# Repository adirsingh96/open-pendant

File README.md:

# OpenPendant

https://github.com/user-attachments/assets/51f84d97-9171-487b-b558-6a6707e0dcb2

The launch film: it listens only when you ask, the meeting stays on your phone, you bring your own keys, and the board, case, and firmware are open source.

Open-source DIY AI audio pendant. Firmware runs on a **Seeed XIAO nRF52840 Sense**. The necklace captures audio and streams 16 kHz PCM over BLE. Speech-to-text runs on the **phone or laptop**. The MCU never holds an API key.

Record only with an obvious LED and an explicit host subscribe (GATT notify on = recording).

## Hardware

| Part | Notes |
|------|--------|
| Seeed XIAO nRF52840 Sense | nRF52840 + onboard PDM mic + LSM6DS3TR-C IMU |
| microSD SPI/SDIO module | 8-pin breakout; VCC = **3V3 only** (never 5V) |
| Ø6 tactile button | 2-pin NO; COM → GND, NO → D1 |
| 22 µF capacitor | Across SD **3V3** and **GND** (16 V ceramic preferred) |
| Perfboard strip | ~8 × 18 holes; XIAO + SD on the front, LiPo on the back |
| WLY602030 1S LiPo | 3.7 V nominal, 300 mAh, 6 × 20 × 30 mm. Open-wire to **BAT+/BAT−**. USB-C charges via BQ25101. |
| USB-C cable | Dev and UF2 flash |

The table above is the first bench build on perfboard. The wearable replaces that strip and the SD breakout with the carrier below. Do not order the older 30 × 45 mm board.

| Build file | What it is |
|------------|------------|
| [`openpendant_carrier-gerbers.zip`](hardware/openpendant_carrier/openpendant_carrier/output/openpendant_carrier-gerbers.zip) | JLCPCB gerbers. Bare boards, 2-layer, 1.6 mm, 1 oz, lead-free HASL. Assembly off. |
| [`openpendant_carrier.kicad_pro`](hardware/openpendant_carrier/openpendant_carrier/openpendant_carrier.kicad_pro) | KiCad source |
| [`docs/carrier_assembly.html`](docs/carrier_assembly.html) | What arrives, what you solder, and the pin map |
| [`cad/character/`](hardware/openpendant_carrier/cad/character/) | Case to print: `character_front.3mf`, `character_back.stl`, `character_button_hat.stl`. Read `PRINT.txt` in that folder. |

Print the character case (Orbit O). PETG, 0.4 mm nozzle, 0.2 mm layers, no supports. Front skirt on the bed. Back chest-down so the chain bail sits on the bed. That folder is the only case in the repo.

Assembly guide for the first perfboard build: [`docs/pendant_assembly.html`](docs/pendant_assembly.html).

### Wiring (USB at the bottom)

Pin map with the component face toward you:

```text
  XIAO                              microSD (SPI)
  ----                              -------------
  D9  (SCK)  ---------------------> CLK
  D8  (MOSI) ---------------------> CMD
  D7  (MISO) ---------------------> D0
  D6  (CS)   ---------------------> D3
  3V3 ----------------------------> 3V3
  GND ----------------------------> GND
                                    D1, D2  (leave open)

  Button NO  ---------------------> D1
  Button COM ---------------------> GND

  22 µF  across SD 3V3 ↔ SD GND

  LiPo red  --> BAT+     (through the BAT window, last)
  LiPo black -> BAT−
```

```text
Left (USB bottom)       Right (USB bottom)
─────────────────       ──────────────────
D6 ──► SD D3 (CS)       D7 ──► SD D0
D5  (IMU SCL — open)    D8 ──► SD CMD
D4  (IMU SDA — open)    D9 ──► SD CLK
D3                      D10
D2                      3V3 ──► SD 3V3
D1  button NO           GND
D0                      5V   (empty)
```

Firmware remaps SPI2 onto **D9 / D8 / D7** (not the board silk SPI defaults D8 / D10 / D9) and disables UART0 so it cannot steal **D6 / D7**. After soldering, flash over USB (no cell required) and run **Settings → Developer → Run SD test** with a FAT32 card.

## What you get

- **Firmware** (Zephyr / nRF Connect SDK 3.4, Zephyr 4.4): BLE GATT PCM + status, IMU still-sleep (mic off when the board is still, wake on motion), battery voltage / SoC estimate, microSD FAT R/W self-test, **offline meeting/note PCM on SD** with BLE sync (`70301105`).
- **Flutter app** in [`app/`](app/): meetings and hold-to-talk notes over BLE, local VAD, **Saaras v4** or on-device **Qwen3-ASR**, reminders, daily briefings and recaps, persistent follow-ups, Memories search, local SQLite, and **pull of offline SD clips on reconnect**. Meetings stay one transcript. Speaker diarization is not applied.
- **Laptop tools** in [`tools/`](tools/): BLE capture to WAV, OpenAI or local Whisper.

Protocol, clip schema, and roadmap: [project_context.md](project_context.md). Later sync sketch: [docs/sync_api.md](docs/sync_api.md).

## Firmware

Requires [nRF Connect SDK v3.4.0](https://docs.nordicsemi.com/bundle/ncs-latest/page/nrf/installation.html). Use the Nordic SoftDevice Controller only — do **not** enable `CONFIG_BT_LL_SW_SPLIT` on this board (USB CDC breaks).

```bash
west build -b xiao_ble/nrf52840/sense -d build .
```

Double-tap RESET so the volume `XIAO-SENSE` appears. Finder copy often fails; `dd` works:

```bash
dd if=$(find build -name zephyr.uf2 | head -1) of=/Volumes/XIAO-SENSE/CURRENT.UF2 bs=4096
```

Serial (macOS `screen` often hangs up CDC):

```bash
python3 -m serial.tools.miniterm /dev/cu.usbmodem1101 115200
```

BLE advertises as **OpenPendant**. Disconnect nRF Connect before the app or laptop capture (one connection).

**Control** UUID `70301104-…`:
- `0` / `1` — find-pendant LED flash off / on
- `2` — SD mount / write / read self-test (result in status bytes 8–9)
- `0x10` — list next pending offline clip (response on SD data notify)
- `0x11` + `id[8]` — open clip for read
- `0x12` + `offset_le32` + `len_le16` — read chunk
- `0x13` + `id[8]` — delete after phone has stored the clip

**SD data** UUID `70301105-…` (NOTIFY/READ): list/read framing for offline sync. Live PCM stays on `70301102`.

**Offline button UX** (when PCM notify is off): single click toggles a meeting session under `/SD:/op/m_…/`; long-press records a note `n_….pcm`. When the phone arms live PCM, offline capture stops (no dual-write).

### Offline → sync test (USB power, no LiPo)

1. FAT32 card in the SPI slot; flash firmware; leave BLE disconnected (or never connect).
2. Offline: click → talk → click (meeting); long-press a note. Red LED while meeting armed; blue while note held.
3. Connect the app → automatic sync (or **Developer → Sync SD**). Meetings/notes appear and transcribe like live captures.
4. Second sync imports nothing (deleted on card / `pendant_clip_id` dedup).
5. Regression: with BLE connected and Record armed, audio streams over PCM notify with **no** new SD writes.
## Flutter app

A meeting stays one transcript. Overview is the short recap, action items, and private notes. Ask about this meeting sits under either tab.

| Transcript | Overview |
|------------|----------|
|  |  |

```bash
cd app
flutter pub get
flutter run -d macos          # BLE works on Mac
# or a physical iPhone / Android — not the iOS simulator
```

Paste a **Sarvam** key in **Settings** (required for cloud transcripts) and an **OpenAI** key for day Clean, Memories, and meeting Recap. Keys stay on the host (Keychain / Keystore / app-support file on desktop), never on the pendant.

**Typical day**

1. Connect. Optional **Calibrate** (wear as usual, read the script) sets a personal VAD floor for **notes** only.
2. Optional **Voices**: enroll up to 4 people (2–10 s sample each). Meetings do not split one clip into speaker turns.
3. Start a **meeting** (pendant click, or **Start meeting** in the app) or take a **note** (hold the pendant ~0.7 s, or **Take a note** on the phone). Say “remind me to … at 10 AM” and the phone notifies 15 minutes before; notes without a time come back in an 8 AM reminder until you check them off. **Double-click** rings the connected phone so you can find it. **Find pendant** (connected sheet or Settings → More) is closer/farther from BLE signal, not a compass. Notify stays on while a meeting is armed; LED stays solid. Chunks rotate on IMU sleep, about 12 s of audio, or quiet after speech. Local VAD skips the cloud when there is no speech. Meetings use a fixed energy floor (`1e9`, ~0.5 s of speech) so people a metre or two from the chest mic still pass; hiss still has to look like voice. Wearer calibrate does not raise that meeting gate. Double-click a meeting title to rename it.
4. **Transcription:** Settings can use **Saaras v4** (cloud) or **on-device Qwen3-ASR**. Both store the engine text as returned (Hindi in Devanagari when that is what came back). Stop the meeting when you are done. Home groups chunks into one transcript. The transcript tab shows **Transcribing…** until STT catches up.
5. **Close the day:** Home surfaces pending notes and open loops. Tap **Close today** to clean the day’s stored text and create chapters, decisions, follow-ups, and a Memories-ready recap. Follow-ups become checkable notes and join the 8 AM digest until completed. Open the saved review and use **Refresh recap** to replace it after recording more; each run uses OpenAI.

More setup (permissions, IMU debug): [app/README.md](app/README.md).

## Laptop capture

```bash
python3 -m pip install -r tools/requirements.txt
export OPENAI_API_KEY=          # optional; omit for local Whisper
python3 tools/capture_pcm.py --seconds 8 --out capture.wav && \
  python3 tools/transcribe.py capture.wav --backend openai
```

Local Whisper:

```bash
python3 tools/transcribe.py capture.wav --backend local
```

## Consent and sleep

- **Recording:** enable PCM notify. The red LED stays solid while subscribed (armed).
- **IMU sleep:** after ~10 s still, firmware stops the PDM mic and PCM. BLE stays up. Motion wakes the mic. Host VAD drops non-speech before STT.
- **App Sleep** is a BLE disconnect, not IMU sleep.

## Battery

Solder the WLY602030 **red** lead to **BAT+** and **black** to **BAT−** (polarity matters; open wire, no JST). USB-C charges the cell through the XIAO BQ25101. Connect the cell **last**, after the SD / button joints meter clean on USB.

The cell has no fuel-gauge IC. Firmware measures pack voltage (P0.31, 1 MΩ / 510 kΩ divider) and the app maps that to a **rough SoC only when USB is unplugged**. On USB the BQ25101 rail reads ~4.1 V even with no cell, so the UI shows **USB** instead of a fake percent. Treat ~20% as “charge soon.” Keep P0.14 low whenever a cell is attached (firmware hog does this) so P0.31 stays within 3.6 V.

## License

[Apache License 2.0](LICENSE).

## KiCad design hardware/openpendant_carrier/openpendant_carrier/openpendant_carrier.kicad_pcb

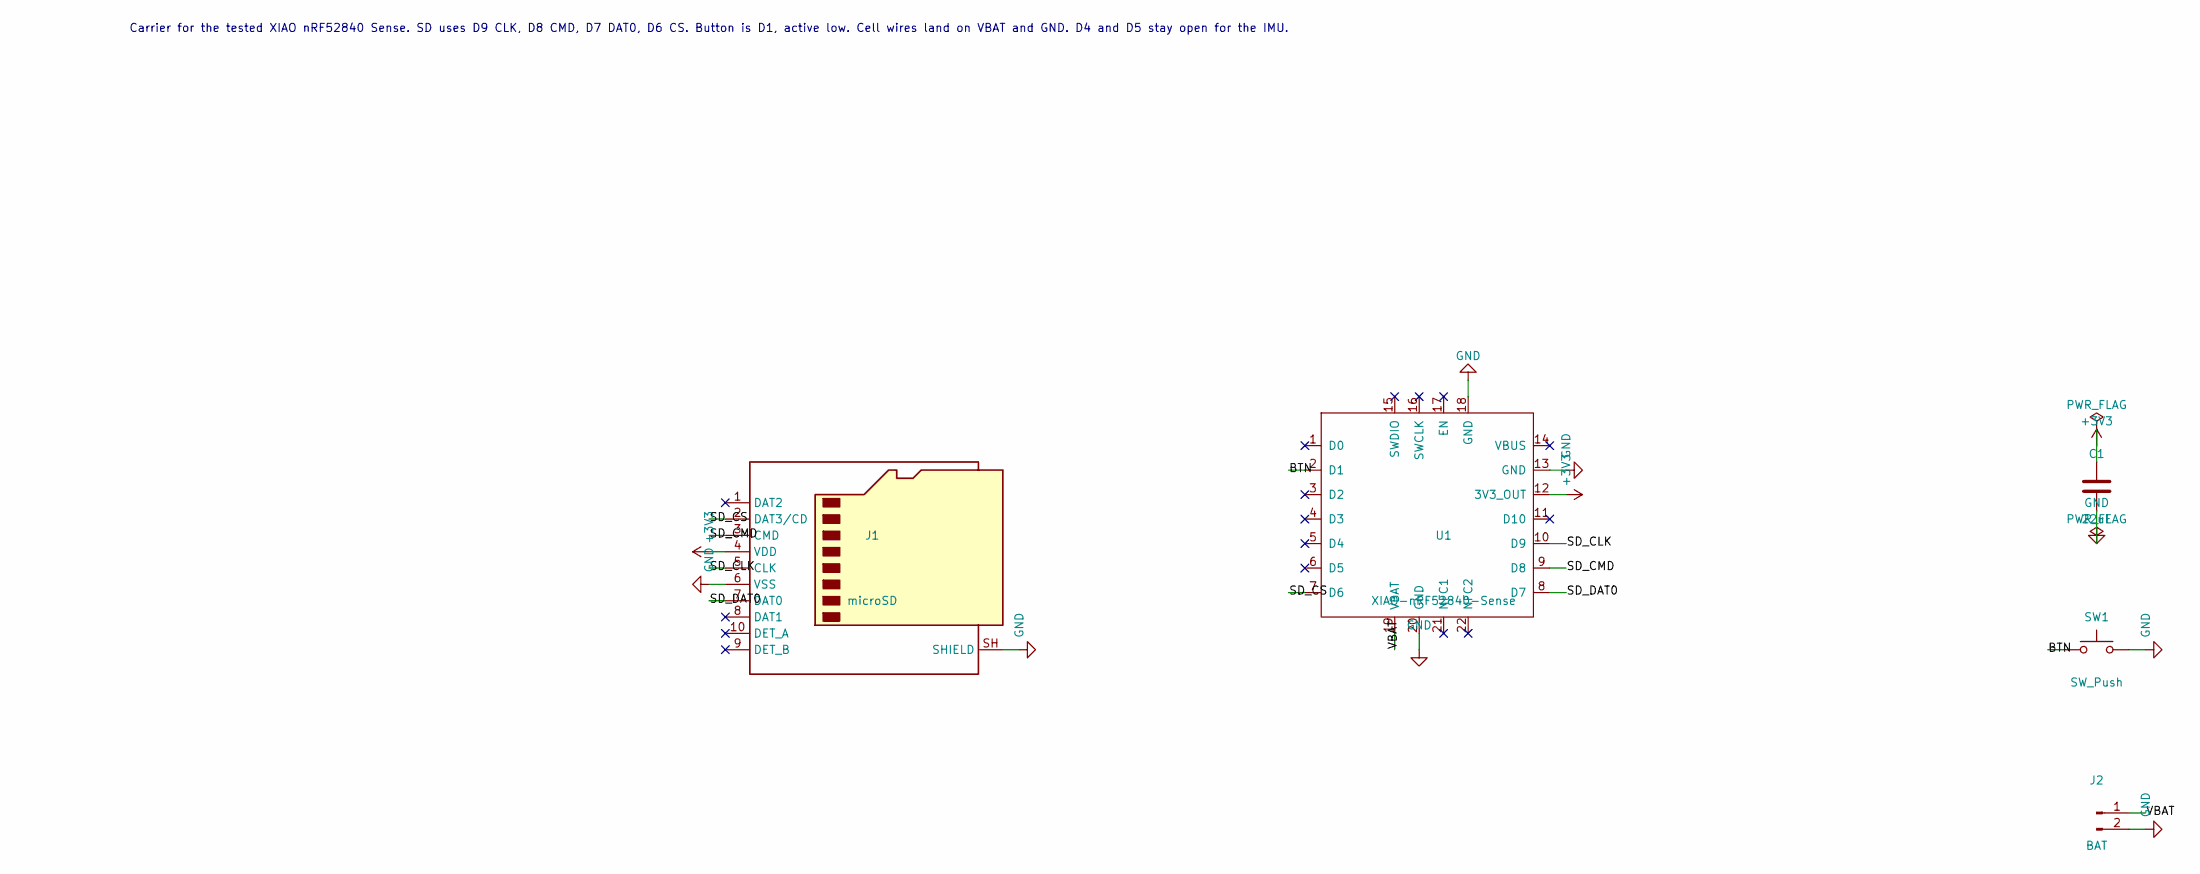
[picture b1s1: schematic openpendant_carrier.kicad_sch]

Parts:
C1: 22uF; C_0805_2012Metric
J1: microSD; microSD_HC_Molex_104031-0811
J2: BAT; BAT_PADS
SW1: SW_Push; SW_SPST_TS-1088-xR020
U1: XIAO-nRF52840-Sense; XIAO-nRF52840-SMD

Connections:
+3V3: C1.1, J1.4 (VDD), U1.12 (3V3_OUT)
/BTN: SW1.1, U1.2 (D1)
/SD_CLK: J1.5 (CLK), U1.10 (D9)
/SD_CMD: J1.3 (CMD), U1.9 (D8)
/SD_CS: J1.2 (DAT3/CD), U1.7 (D6)
/SD_DAT0: J1.7 (DAT0), U1.8 (D7)
/VBAT: J2.1, U1.19 (VBAT)
GND: C1.2, J1.6 (VSS), J1.SH (SHIELD), J2.2, SW1.2, U1.13 (GND), U1.18 (GND), U1.20 (GND)

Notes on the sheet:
Carrier for the tested XIAO nRF52840 Sense. SD uses D9 CLK, D8 CMD, D7 DAT0, D6 CS. Button is D1, active low. Cell wires land on VBAT and GND. D4 and D5 stay open for the IMU.

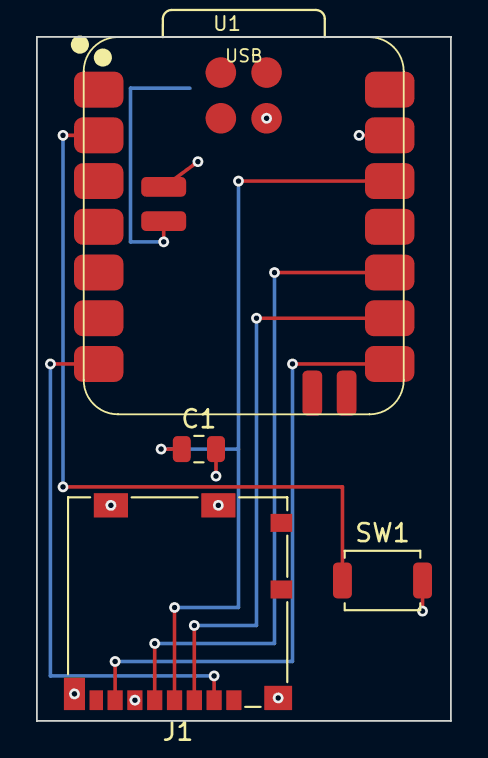
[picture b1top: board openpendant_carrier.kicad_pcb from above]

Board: 2 copper layers, 23.0 x 38.0 mm, 5 parts (0 on the bottom side), 8 nets.
